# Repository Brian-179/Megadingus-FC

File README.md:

# Megadingus-FC
Megadingus flight controllers/altimeters

(OUTDATED) FC1.5: Mostly tested, i2C bus is having an error, SPI untested and UART/USB works fine.

FC2.1: Fully ground tested but not flight proven under TVC. TVC flight imminent.

3 pyro channels

WiFi (ESP8266)

Main MCU is an RP2040

Main power connector is an XT30 (2-5S, 6S if you're willing to take the risk)

USB Mini B port

BMI088 IMU, BME280 Barometer

3 servo outputs

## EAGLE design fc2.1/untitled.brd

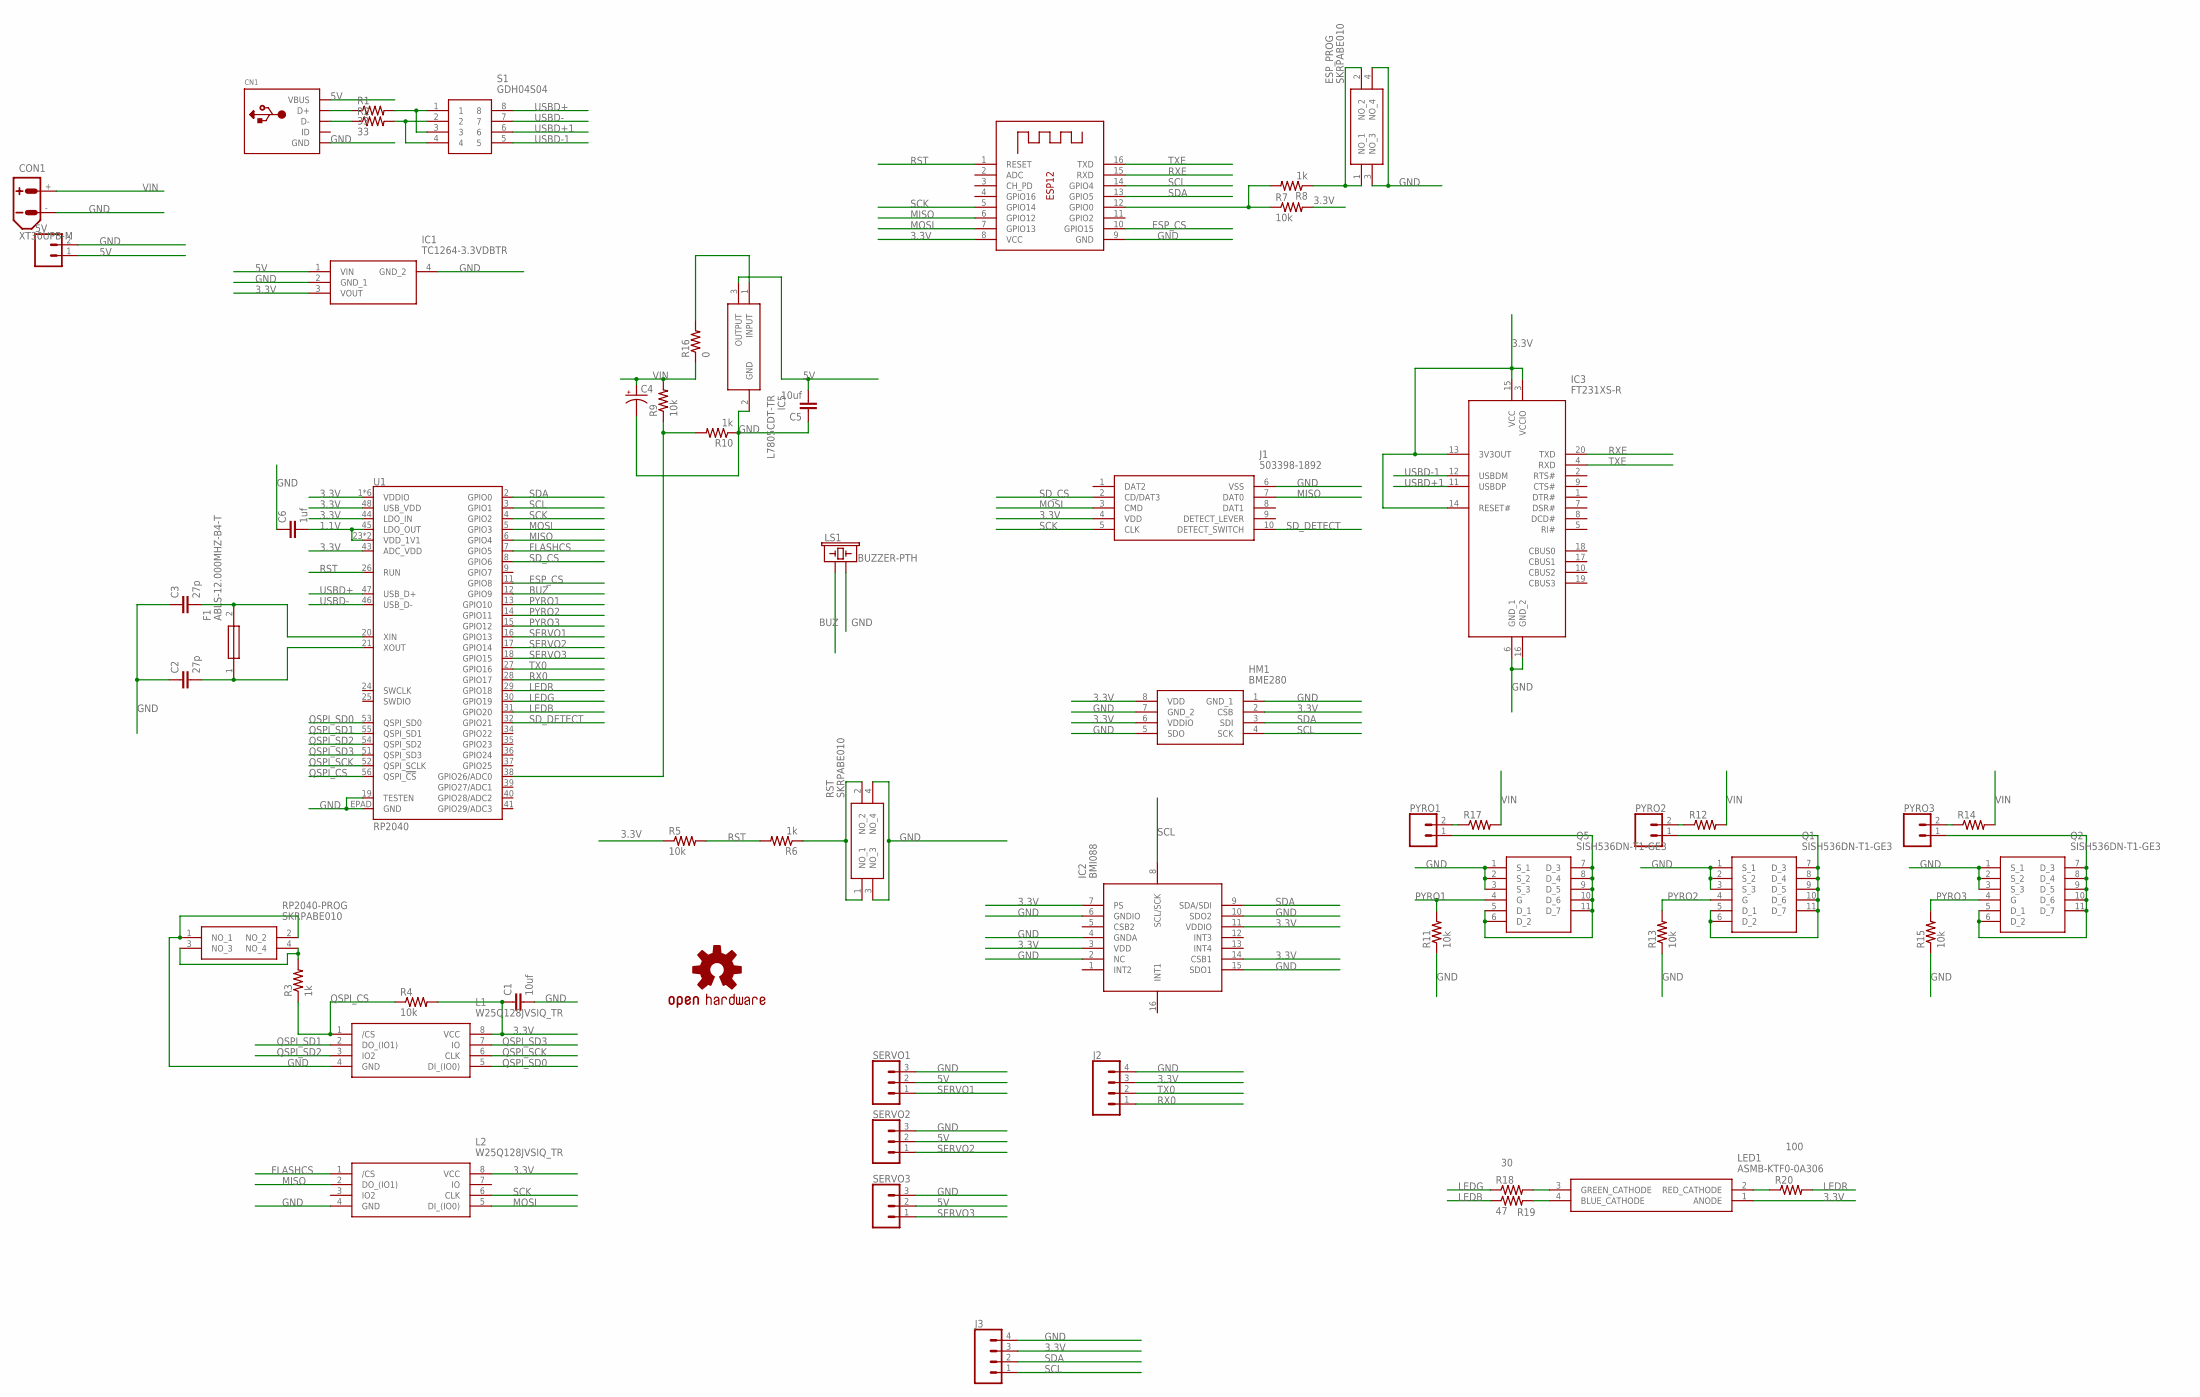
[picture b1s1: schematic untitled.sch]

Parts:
5V: CONN_02; 1X02
C1, C5: 10uf; C0805
C2, C3: 27p; C0805
C4: CPOL-USE3.5-8; E3,5-8
C6: 1uf; C0805
CN1: USBMINIB; USB-MINIB
CON1: XT30UPB-M
ESP_PROG: SKRPABE010
F1: ABLS-12.000MHZ-B4-T; HC/49US-(AT49)_1
HM1: BME280
IC1: TC1264-3.3VDBTR; SOT230P700X180-4N
IC2: BMI088
IC3: FT231XS-R; SOP64P599X175-20N
IC5: L7805CDT-TR; L7805CDTTR
J1: 503398-1892
J2, J3: CONN_04; 1X04
L1, L2: W25Q128JVSIQ_TR; SOIC127P780X195-8N
LED1: ASMB-KTF0-0A306; ASMBKTF00A306
LOGO1: OSHW-LOGOS; OSHW-LOGO-S
LS1: BUZZER-PTH; BUZZER-12MM
PYRO1, PYRO2, PYRO3: CONN_025MM; SCREWTERMINAL-5MM-2
Q1, Q2, Q5: SISH536DN-T1-GE3; SQSA80ENWT1_GE3
R1, R2: 33; M0805
R3, R6, R8, R10: 1k; M0805
R4, R5, R7, R9, R11, R13, R15: 10k; M0805
R12, R14, R16, R17: 0; R2512
R18: 30; M0805
R19: 47; M0805
R20: 100; M0805
RP2040-PROG: SKRPABE010
RST: SKRPABE010
S1: GDH04S04; SOIC127P813X256-8N
SERVO1, SERVO2, SERVO3: CONN_03; 1X03
U1: RP2040; QFN-56
X1: ESP-12

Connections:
1.1V: C6.2, U1.23 (VDD_1V1), U1.45 (LDO_OUT), U1.50 (VDD_1V1)
3.3V: C1.1, HM1.2 (CSB), HM1.6 (VDDIO), HM1.8 (VDD), IC1.3 (VOUT), IC2.3 (VDD), IC2.7 (PS), IC2.11 (VDDIO), IC2.14 (CSB1), IC3.3 (VCCIO), IC3.13 (3V3OUT), IC3.14 (RESET#), IC3.15 (VCC), J1.4 (VDD), J2.3, J3.3, L1.8 (VCC), L2.8 (VCC), LED1.1 (ANODE), R4.2, R5.1, R7.2, U1.1 (VDDIO), U1.10 (VDDIO), U1.22 (VDDIO), U1.33 (VDDIO), U1.42 (VDDIO), U1.43 (ADC_VDD), U1.44 (LDO_IN), U1.48 (USB_VDD), U1.49 (VDDIO), X1.8 (VCC)
5V: 5V.1, C5.2, CN1.VBUS, IC1.1 (VIN), IC5.3 (OUTPUT), SERVO1.2, SERVO2.2, SERVO3.2
BUZ: LS1.+ (1), U1.12 (GPIO9)
ESP_CS: U1.11 (GPIO8), X1.10 (GPIO15)
FLASHCS: L2.1 (/CS), U1.7 (GPIO5)
GND: 5V.2, C1.2, C2.1, C3.1, C4.-, C5.1, C6.1, CN1.GND, CON1.-, ESP_PROG.3 (NO_3), ESP_PROG.4 (NO_4), HM1.1 (GND_1), HM1.5 (SDO), HM1.7 (GND_2), IC1.2 (GND_1), IC1.4 (GND_2), IC2.2 (NC), IC2.4 (GNDA), IC2.6 (GNDIO), IC2.10 (SDO2), IC2.15 (SDO1), IC3.6 (GND_1), IC3.16 (GND_2), IC5.2 (GND), J1.6 (VSS), J2.4, J3.4, L1.4 (GND), L2.4 (GND), LS1.- (2), Q1.1 (S_1), Q1.2 (S_2), Q1.3 (S_3), Q2.1 (S_1), Q2.2 (S_2), Q2.3 (S_3), Q5.1 (S_1), Q5.2 (S_2), Q5.3 (S_3), R10.1, R11.1, R13.1, R15.1, RP2040-PROG.1 (NO_1), RP2040-PROG.2 (NO_2), RST.3 (NO_3), RST.4 (NO_4), SERVO1.3, SERVO2.3, SERVO3.3, U1.19 (TESTEN), U1.EPAD (GND), X1.9 (GND)
LEDB: R19.1, U1.31 (GPIO20)
LEDG: R18.1, U1.30 (GPIO19)
LEDR: R20.2, U1.29 (GPIO18)
MISO: J1.7 (DAT0), L2.2 (DO_(IO1)), U1.6 (GPIO4), X1.6 (GPIO12)
MOSI: J1.3 (CMD), L2.5 (DI_(IO0)), U1.5 (GPIO3), X1.7 (GPIO13)
unnamed: PYRO2.2, R12.1
unnamed: R3.2, RP2040-PROG.3 (NO_3), RP2040-PROG.4 (NO_4)
unnamed: ESP_PROG.1 (NO_1), ESP_PROG.2 (NO_2), R8.1
unnamed: R6.1, RST.1 (NO_1), RST.2 (NO_2)
unnamed: CN1.D+, R1.1
unnamed: CN1.D-, R2.1
unnamed: PYRO2.1, Q1.5 (D_1), Q1.6 (D_2), Q1.7 (D_3), Q1.8 (D_4), Q1.9 (D_5), Q1.10 (D_6), Q1.11 (D_7)
unnamed: PYRO3.2, R14.1
unnamed: PYRO1.1, Q5.5 (D_1), Q5.6 (D_2), Q5.7 (D_3), Q5.8 (D_4), Q5.9 (D_5), Q5.10 (D_6), Q5.11 (D_7)
unnamed: R7.1, R8.2, X1.12 (GPIO0)
unnamed: PYRO3.1, Q2.5 (D_1), Q2.6 (D_2), Q2.7 (D_3), Q2.8 (D_4), Q2.9 (D_5), Q2.10 (D_6), Q2.11 (D_7)
unnamed: R1.2, S1.1, S1.3
unnamed: IC5.1 (INPUT), R16.2
unnamed: PYRO1.2, R17.1
unnamed: R2.2, S1.2, S1.4
unnamed: C3.2, F1.2, U1.20 (XIN)
unnamed: C2.2, F1.1, U1.21 (XOUT)
unnamed: LED1.3 (GREEN_CATHODE), R18.2
unnamed: R9.1, R10.2, U1.38 (GPIO26/ADC0)
unnamed: LED1.4 (BLUE_CATHODE), R19.2
unnamed: LED1.2 (RED_CATHODE), R20.1
PYRO1: Q5.4 (G), R11.2, U1.13 (GPIO10)
PYRO2: Q1.4 (G), R13.2, U1.14 (GPIO11)
PYRO3: Q2.4 (G), R15.2, U1.15 (GPIO12)
QSPI_CS: L1.1 (/CS), R3.1, R4.1, U1.56 (QSPI_!CS!)
QSPI_SCK: L1.6 (CLK), U1.52 (QSPI_SCLK)
QSPI_SD0: L1.5 (DI_(IO0)), U1.53 (QSPI_SD0)
QSPI_SD1: L1.2 (DO_(IO1)), U1.55 (QSPI_SD1)
QSPI_SD2: L1.3 (IO2), U1.54 (QSPI_SD2)
QSPI_SD3: L1.7 (IO), U1.51 (QSPI_SD3)
RST: R5.2, R6.2, U1.26 (RUN), X1.1 (RESET)
RX0: J2.1, U1.28 (GPIO17)
RXE: IC3.20 (TXD), X1.15 (RXD)
SCK: J1.5 (CLK), L2.6 (CLK), U1.4 (GPIO2), X1.5 (GPIO14)
SCL: HM1.4 (SCK), IC2.8 (SCL/SCK), J3.1, U1.3 (GPIO1), X1.14 (GPIO4)
SDA: HM1.3 (SDI), IC2.9 (SDA/SDI), J3.2, U1.2 (GPIO0), X1.13 (GPIO5)
SD_CS: J1.2 (CD/DAT3), U1.8 (GPIO6)
SD_DETECT: J1.10 (DETECT_SWITCH), U1.32 (GPIO21)
SERVO1: SERVO1.1, U1.16 (GPIO13)
SERVO2: SERVO2.1, U1.17 (GPIO14)
SERVO3: SERVO3.1, U1.18 (GPIO15)
TX0: J2.2, U1.27 (GPIO16)
TXE: IC3.4 (RXD), X1.16 (TXD)
USBD+: S1.8, U1.47 (USB_D+)
USBD+1: IC3.11 (USBDP), S1.6
USBD-: S1.7, U1.46 (USB_D-)
USBD-1: IC3.12 (USBDM), S1.5
VIN: C4.+, CON1.+, R9.2, R12.2, R14.2, R16.1, R17.2

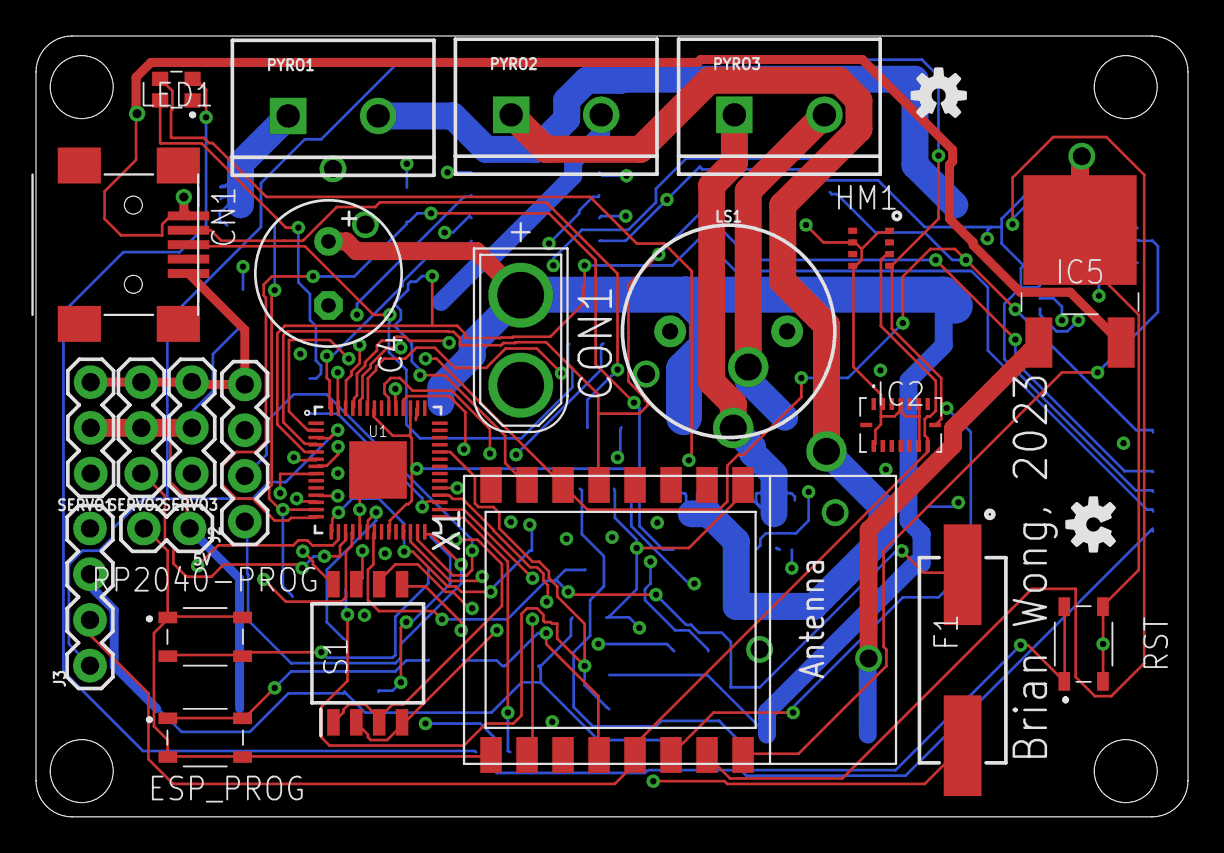
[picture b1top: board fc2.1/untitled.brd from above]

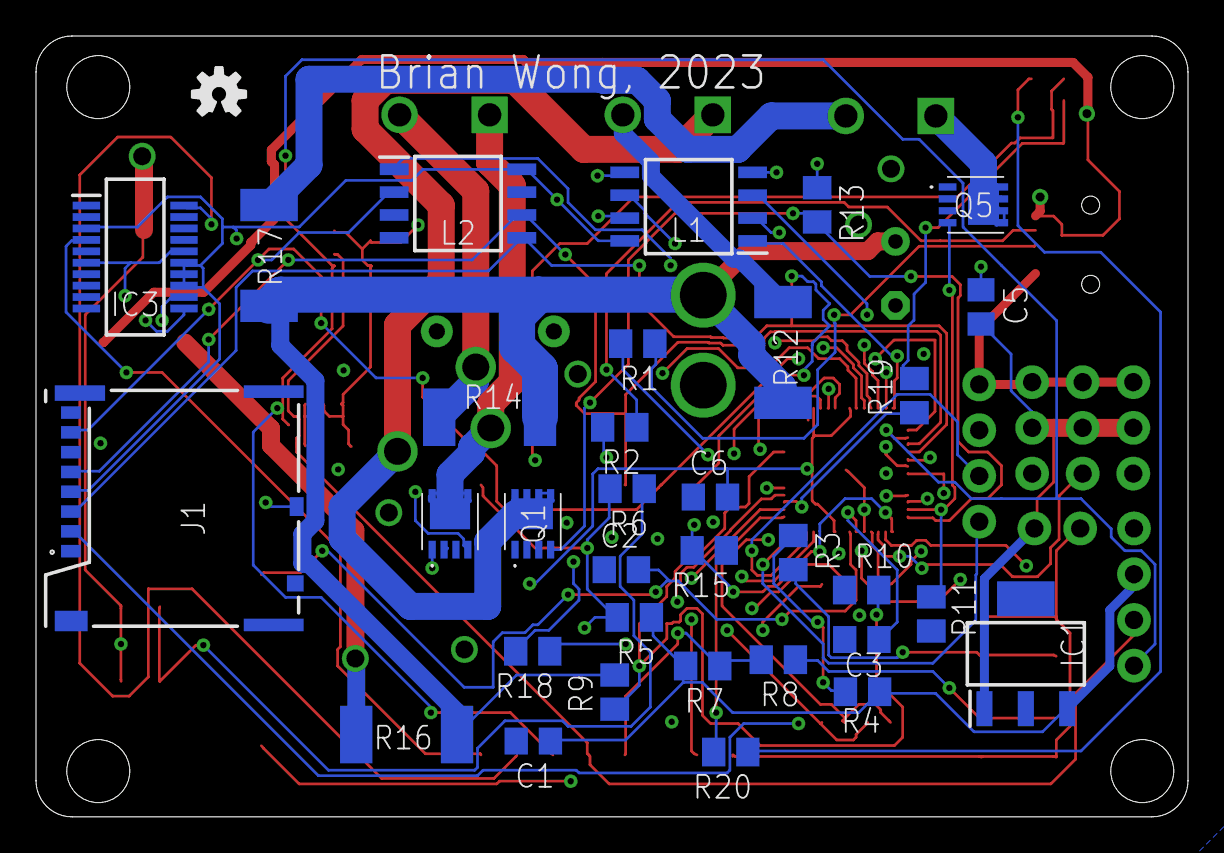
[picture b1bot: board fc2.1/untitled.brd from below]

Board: 4 copper layers, 64.0 x 43.4 mm, 60 parts (34 on the bottom side), 60 nets.

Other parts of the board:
LOGO2, LOGO3: OSHW-LOGOS; OSHW-LOGO-S

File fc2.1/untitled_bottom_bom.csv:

Comment,Designator,Footprint,LCSC Part #
0,R12 R14 R16 R17,R2512,
1k,R3 R6 R8 R10,M0805,
1uf,C6,C0805,
10k,R4 R5 R7 R9 R11 R13 R15,M0805,
10uf,C1 C5,C0805,
27p,C2 C3,C0805,
30,R18,M0805,
33,R1 R2,M0805,
47,R19,M0805,
100,R20,M0805,
503398-1892,J1,503398-1892,
FT231XS-R,IC3,SOP64P599X175-20N,
SISH536DN-T1-GE3,Q1 Q2 Q5,SQSA80ENWT1_GE3,
TC1264-3.3VDBTR,IC1,SOT230P700X180-4N,
W25Q128JVSIQ_TR,L1 L2,SOIC127P780X195-8N,

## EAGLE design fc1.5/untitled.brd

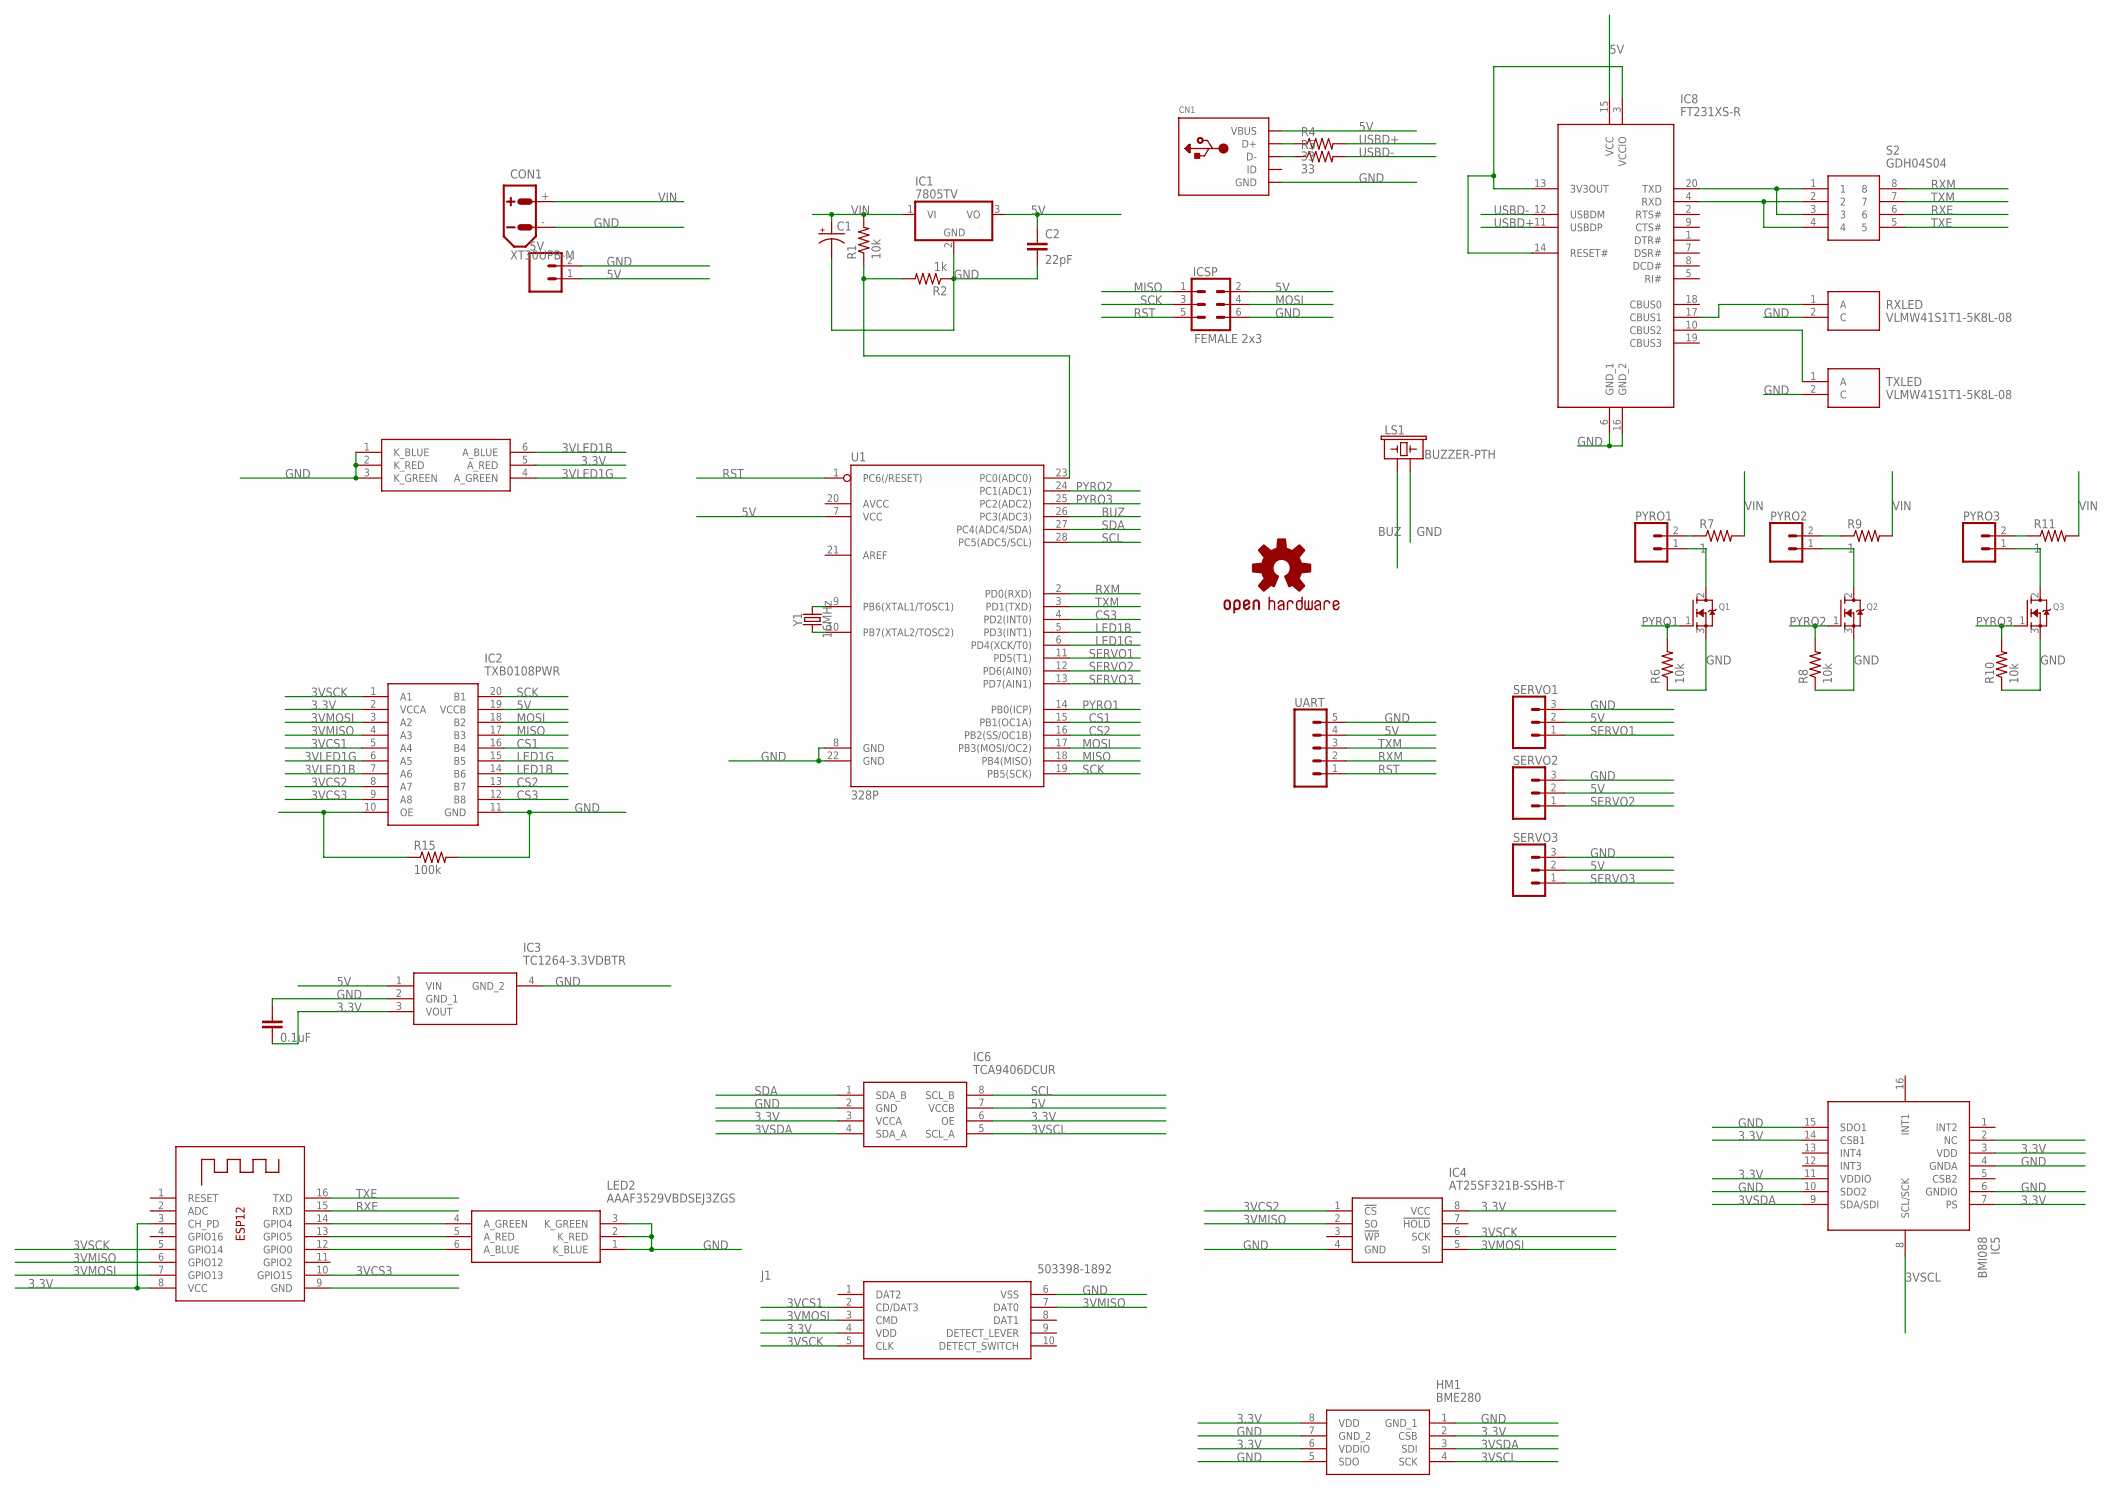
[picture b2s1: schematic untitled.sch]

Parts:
5V: CONN_02; 1X02
C1: CPOL-USE3.5-8; E3,5-8
C2: 22pF; CAP-PTH-2.54
C4: 0.1uF; CAP-PTH-SMALL-KIT
CN1: USBMINIB; USB-MINIB
CON1: XT30UPB-M
HM1: BME280
IC1: 7805TV; TO220V
IC2: TXB0108PWR; SOP65P640X120-20N
IC3: TC1264-3.3VDBTR; SOT230P700X180-4N
IC4: AT25SF321B-SSHB-T; SOIC127P600X175-8N
IC5: BMI088
IC6: TCA9406DCUR; SOP50P310X90-8N
IC8: FT231XS-R; SOP64P599X175-20N
ICSP: FEMALE 2x3; 2X3
J1: 503398-1892
LED1, LED2: AAAF3529VBDSEJ3ZGS
LOGO1: OSHW-LOGOL; OSHW-LOGO-L
LS1: BUZZER-PTH; BUZZER-12MM
PYRO1, PYRO2, PYRO3: CONN_025MM; SCREWTERMINAL-5MM-2
Q1, Q2, Q3: MOSFET-NGDS_TO220V; TO220V
R1, R6, R8, R10: 10k; 0805-THM
R2: 1k; 0805-THM
R4, R5: 33; 0805-THM
R7, R9, R11: 1; 0805-THM
R15: 100k; 0805-THM
RXLED: VLMW41S1T1-5K8L-08; LEDM3528X185N
S2: GDH04S04; SOIC127P813X256-8N
SERVO1, SERVO2, SERVO3: CONN_03; 1X03
TXLED: VLMW41S1T1-5K8L-08; LEDM3528X185N
U1: 328P; DIP28
UART: CONN_05; 1X05
X1: ESP-12
Y1: 16MHz; HC49US

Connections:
3.3V: C4.2, HM1.2 (CSB), HM1.6 (VDDIO), HM1.8 (VDD), IC2.2 (VCCA), IC3.3 (VOUT), IC4.8 (VCC), IC5.3 (VDD), IC5.7 (PS), IC5.11 (VDDIO), IC5.14 (CSB1), IC6.3 (VCCA), IC6.6 (OE), J1.4 (VDD), LED1.5 (A_RED), X1.3 (CH_PD), X1.8 (VCC)
3VCS1: IC2.5 (A4), J1.2 (CD/DAT3)
3VCS2: IC2.8 (A7), IC4.1 (!CS)
3VCS3: IC2.9 (A8), X1.10 (GPIO15)
3VLED1B: IC2.7 (A6), LED1.6 (A_BLUE)
3VLED1G: IC2.6 (A5), LED1.4 (A_GREEN)
3VMISO: IC2.4 (A3), IC4.2 (SO), J1.7 (DAT0), X1.6 (GPIO12)
3VMOSI: IC2.3 (A2), IC4.5 (SI), J1.3 (CMD), X1.7 (GPIO13)
3VSCK: IC2.1 (A1), IC4.6 (SCK), J1.5 (CLK), X1.5 (GPIO14)
3VSCL: HM1.4 (SCK), IC5.8 (SCL/SCK), IC6.5 (SCL_A)
3VSDA: HM1.3 (SDI), IC5.9 (SDA/SDI), IC6.4 (SDA_A)
5V: 5V.1, C2.1, CN1.VBUS, IC1.3 (VO), IC2.19 (VCCB), IC3.1 (VIN), IC6.7 (VCCB), IC8.15 (VCC), ICSP.2, SERVO1.2, SERVO2.2, SERVO3.2, U1.7 (VCC), UART.4
BUZ: LS1.+ (1), U1.26 (PC3(ADC3))
CS1: IC2.16 (B4), U1.15 (PB1(OC1A))
CS2: IC2.13 (B7), U1.16 (PB2(SS/OC1B))
CS3: IC2.12 (B8), U1.4 (PD2(INT0))
GND: 5V.2, C1.-, C2.2, C4.1, CN1.GND, CON1.-, HM1.1 (GND_1), HM1.5 (SDO), HM1.7 (GND_2), IC1.2 (GND), IC2.11 (GND), IC3.2 (GND_1), IC3.4 (GND_2), IC4.4 (GND), IC5.4 (GNDA), IC5.6 (GNDIO), IC5.10 (SDO2), IC5.15 (SDO1), IC6.2 (GND), IC8.6 (GND_1), IC8.16 (GND_2), ICSP.6, J1.6 (VSS), LED1.1 (K_BLUE), LED1.2 (K_RED), LED1.3 (K_GREEN), LED2.1 (K_BLUE), LED2.2 (K_RED), LED2.3 (K_GREEN), LS1.- (2), Q1.3 (S), Q2.3 (S), Q3.3 (S), R2.1, R6.1, R8.1, R10.1, R15.2, RXLED.2 (C), SERVO1.3, SERVO2.3, SERVO3.3, TXLED.2 (C), U1.8 (GND), U1.22 (GND), UART.5, X1.9 (GND)
LED1B: IC2.14 (B6), U1.5 (PD3(INT1))
LED1G: IC2.15 (B5), U1.6 (PD4(XCK/T0))
MISO: IC2.17 (B3), ICSP.1, U1.18 (PB4(MISO))
MOSI: IC2.18 (B2), ICSP.4, U1.17 (PB3(MOSI/OC2))
unnamed: U1.9 (PB6(XTAL1/TOSC1)), Y1.2
unnamed: U1.10 (PB7(XTAL2/TOSC2)), Y1.1
unnamed: R1.1, R2.2, U1.23 (PC0(ADC0))
unnamed: CN1.D+, R4.1
unnamed: IC8.17 (CBUS1), RXLED.1 (A)
unnamed: IC8.20 (TXD), S2.1, S2.3
unnamed: IC8.4 (RXD), S2.2, S2.4
unnamed: IC8.3 (VCCIO), IC8.13 (3V3OUT), IC8.14 (RESET#)
unnamed: CN1.D-, R5.1
unnamed: IC8.10 (CBUS2), TXLED.1 (A)
unnamed: LED2.4 (A_GREEN), X1.14 (GPIO4)
unnamed: LED2.5 (A_RED), X1.13 (GPIO5)
unnamed: IC2.10 (OE), R15.1
unnamed: PYRO1.1, Q1.2 (D)
unnamed: PYRO1.2, R7.1
unnamed: PYRO2.1, Q2.2 (D)
unnamed: PYRO2.2, R9.1
unnamed: PYRO3.1, Q3.2 (D)
unnamed: PYRO3.2, R11.1
unnamed: LED2.6 (A_BLUE), X1.12 (GPIO0)
PYRO1: Q1.1 (G), R6.2, U1.14 (PB0(ICP))
PYRO2: Q2.1 (G), R8.2, U1.24 (PC1(ADC1))
PYRO3: Q3.1 (G), R10.2, U1.25 (PC2(ADC2))
RST: ICSP.5, U1.1 (PC6(/RESET)), UART.1
RXE: S2.6, X1.15 (RXD)
RXM: S2.8, U1.2 (PD0(RXD)), UART.2
SCK: IC2.20 (B1), ICSP.3, U1.19 (PB5(SCK))
SCL: IC6.8 (SCL_B), U1.28 (PC5(ADC5/SCL))
SDA: IC6.1 (SDA_B), U1.27 (PC4(ADC4/SDA))
SERVO1: SERVO1.1, U1.11 (PD5(T1))
SERVO2: SERVO2.1, U1.12 (PD6(AIN0))
SERVO3: SERVO3.1, U1.13 (PD7(AIN1))
TXE: S2.5, X1.16 (TXD)
TXM: S2.7, U1.3 (PD1(TXD)), UART.3
USBD+: IC8.11 (USBDP), R4.2
USBD-: IC8.12 (USBDM), R5.2
VIN: C1.+, CON1.+, IC1.1 (VI), R1.2, R7.2, R9.2, R11.2

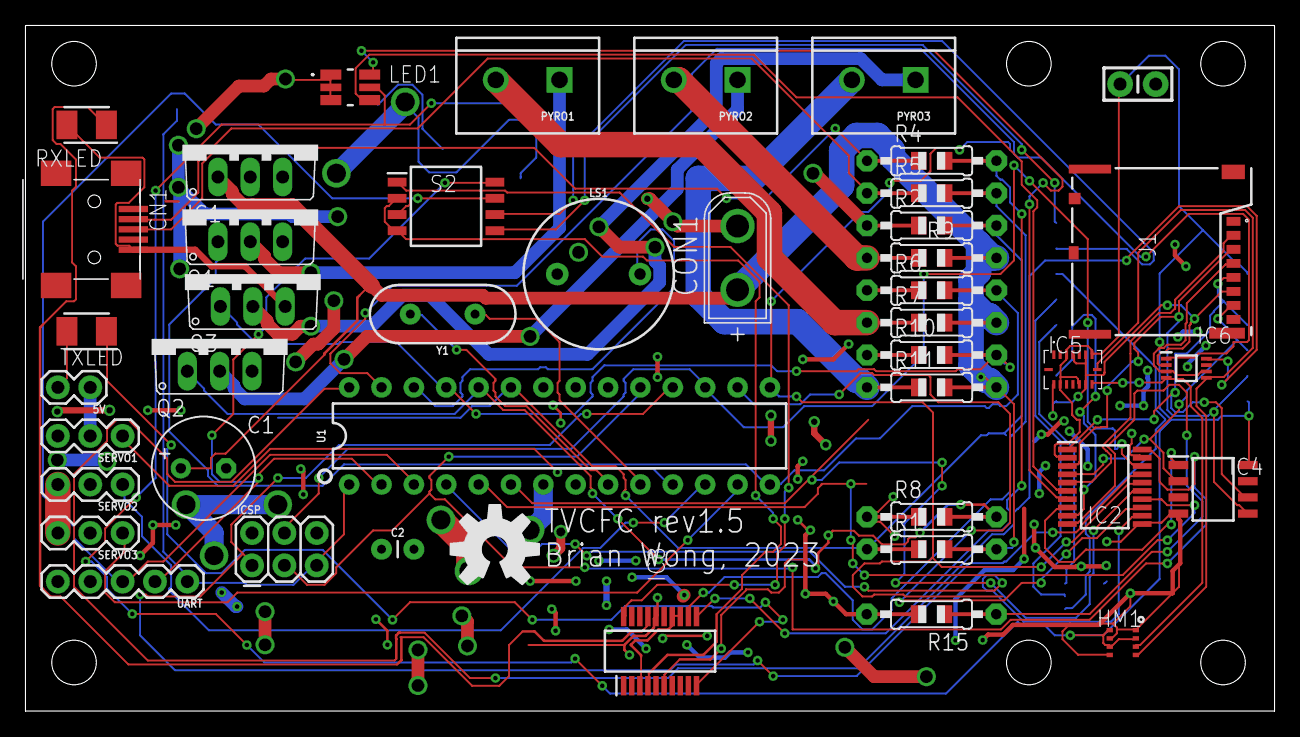
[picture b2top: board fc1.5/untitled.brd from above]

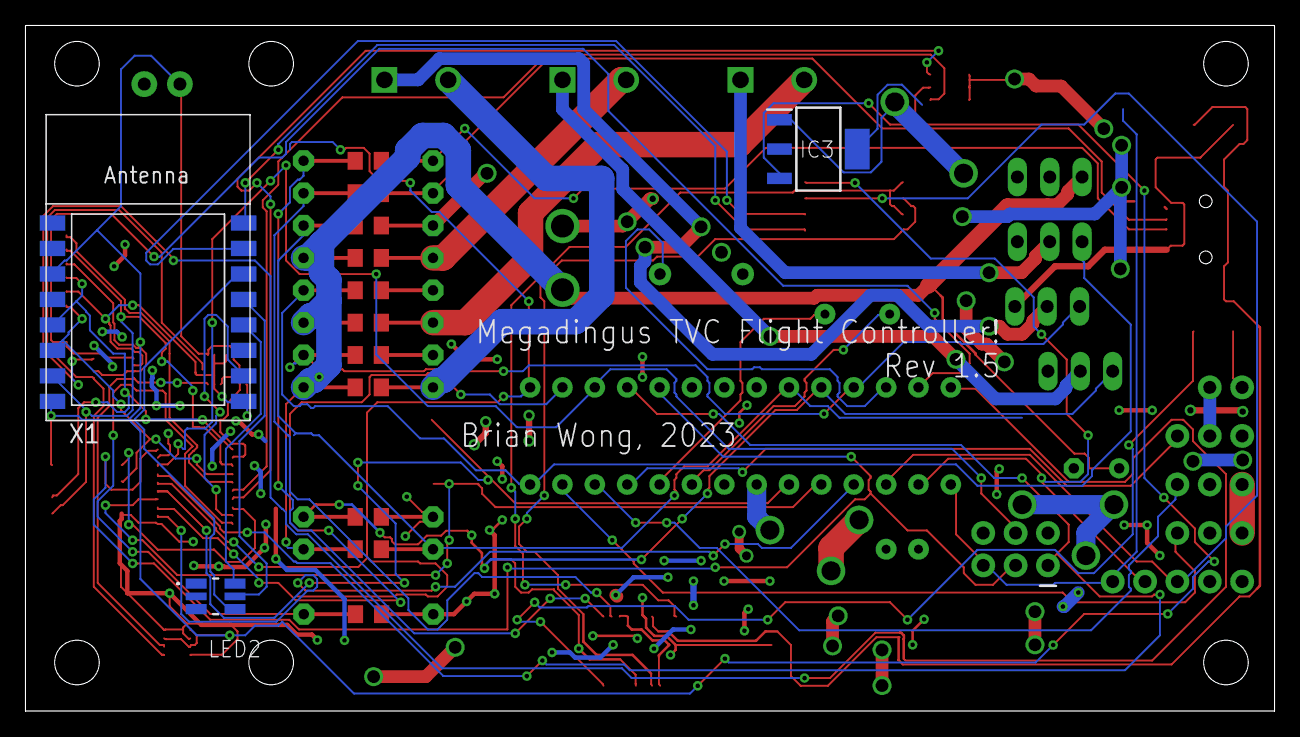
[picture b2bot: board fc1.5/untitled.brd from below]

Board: 2 copper layers, 98.0 x 53.8 mm, 47 parts (3 on the bottom side), 58 nets.

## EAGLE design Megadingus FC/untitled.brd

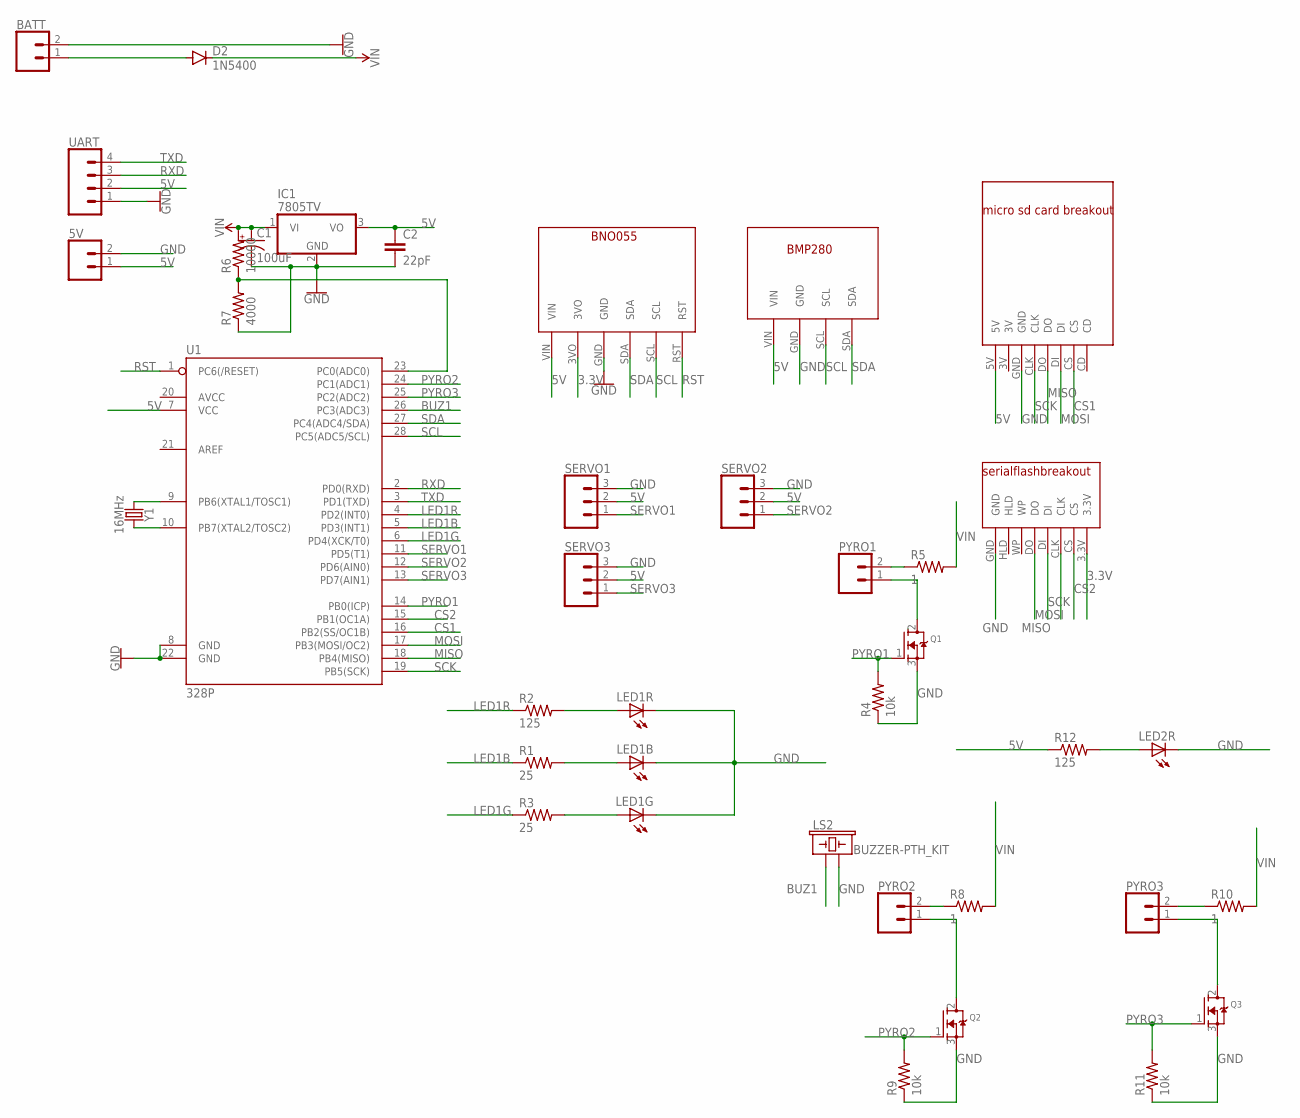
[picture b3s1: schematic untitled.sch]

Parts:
5V: CONN_02; 1X02
BATT: CONN_02; 1X02
C1: 100uF; CPOL-RADIAL-2.5MM-6.5MM
C2: 22pF; CAP-PTH-2.54
D2: 1N5400; DO201-15
IC1: 7805TV; TO220V
LED1B: LED1B; LED5MM
LED1G: LED1G; LED5MM
LED1R, LED2R: LED1R; LED5MM
LS2: BUZZER-PTH_KIT; BUZZER-12MM-KIT
PYRO1, PYRO2, PYRO3: CONN_02; 1X02
Q1, Q2, Q3: MOSFET-NGDS_TO220V; TO220V
R1, R3: 25; 0805-THM
R2, R12: 125; 0805-THM
R4, R9, R11: 10k; 0805-THM
R5, R8, R10: 1; 0805-THM
R6: 10000; 0805-THM
R7: 4000; 0805-THM
SERVO1, SERVO2, SERVO3: CONN_03; 1X03
U1: 328P; DIP28
U$1: BNO055
U$2: BMP280
U$3: ADAFRUITSDCARD
U$4: SPARKFUNFLASHBREAKOUT
UART: CONN_04PTH; 1X04
Y1: 16MHz; HC49US

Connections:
3.3V: U$1.3VO, U$4.3.3V
5V: 5V.1, C2.1, IC1.3 (VO), R12.1, SERVO1.2, SERVO2.2, SERVO3.2, U1.7 (VCC), U$1.VIN, U$2.VIN, U$3.5V, UART.2
BUZ1: LS2.+ (1), U1.26 (PC3(ADC3))
CS1: U1.16 (PB2(SS/OC1B)), U$3.CS
CS2: U1.15 (PB1(OC1A)), U$4.CS
GND: 5V.2, BATT.2, C1.2 (-), C2.2, IC1.2 (GND), LED1B.K (C), LED1G.K (C), LED1R.K (C), LED2R.K (C), LS2.- (2), Q1.3 (S), Q2.3 (S), Q3.3 (S), R4.1, R7.1, R9.1, R11.1, SERVO1.3, SERVO2.3, SERVO3.3, U1.8 (GND), U1.22 (GND), U$1.GND, U$2.GND, U$3.GND, U$4.GND, UART.1
LED1B: R1.1, U1.5 (PD3(INT1))
LED1G: R3.1, U1.6 (PD4(XCK/T0))
LED1R: R2.1, U1.4 (PD2(INT0))
MISO: U1.18 (PB4(MISO)), U$3.DO, U$4.DO
MOSI: U1.17 (PB3(MOSI/OC2)), U$3.DI, U$4.DI
unnamed: PYRO1.1, Q1.2 (D)
unnamed: LED1R.A, R2.2
unnamed: LED1B.A, R1.2
unnamed: LED1G.A, R3.2
unnamed: PYRO1.2, R5.1
unnamed: R6.1, R7.2, U1.23 (PC0(ADC0))
unnamed: U1.9 (PB6(XTAL1/TOSC1)), Y1.1
unnamed: U1.10 (PB7(XTAL2/TOSC2)), Y1.2
unnamed: BATT.1, D2.A
unnamed: PYRO2.2, R8.1
unnamed: PYRO3.2, R10.1
unnamed: PYRO2.1, Q2.2 (D)
unnamed: PYRO3.1, Q3.2 (D)
unnamed: LED2R.A, R12.2
PYRO1: Q1.1 (G), R4.2, U1.14 (PB0(ICP))
PYRO2: Q2.1 (G), R9.2, U1.24 (PC1(ADC1))
PYRO3: Q3.1 (G), R11.2, U1.25 (PC2(ADC2))
RST: U1.1 (PC6(/RESET)), U$1.RST
RXD: U1.2 (PD0(RXD)), UART.3
SCK: U1.19 (PB5(SCK)), U$3.CLK, U$4.CLK
SCL: U1.28 (PC5(ADC5/SCL)), U$1.SCL, U$2.SCL
SDA: U1.27 (PC4(ADC4/SDA)), U$1.SDA, U$2.SDA
SERVO1: SERVO1.1, U1.11 (PD5(T1))
SERVO2: SERVO2.1, U1.12 (PD6(AIN0))
SERVO3: SERVO3.1, U1.13 (PD7(AIN1))
TXD: U1.3 (PD1(TXD)), UART.4
VIN: C1.1 (+), D2.C, IC1.1 (VI), R5.2, R6.2, R8.2, R10.2

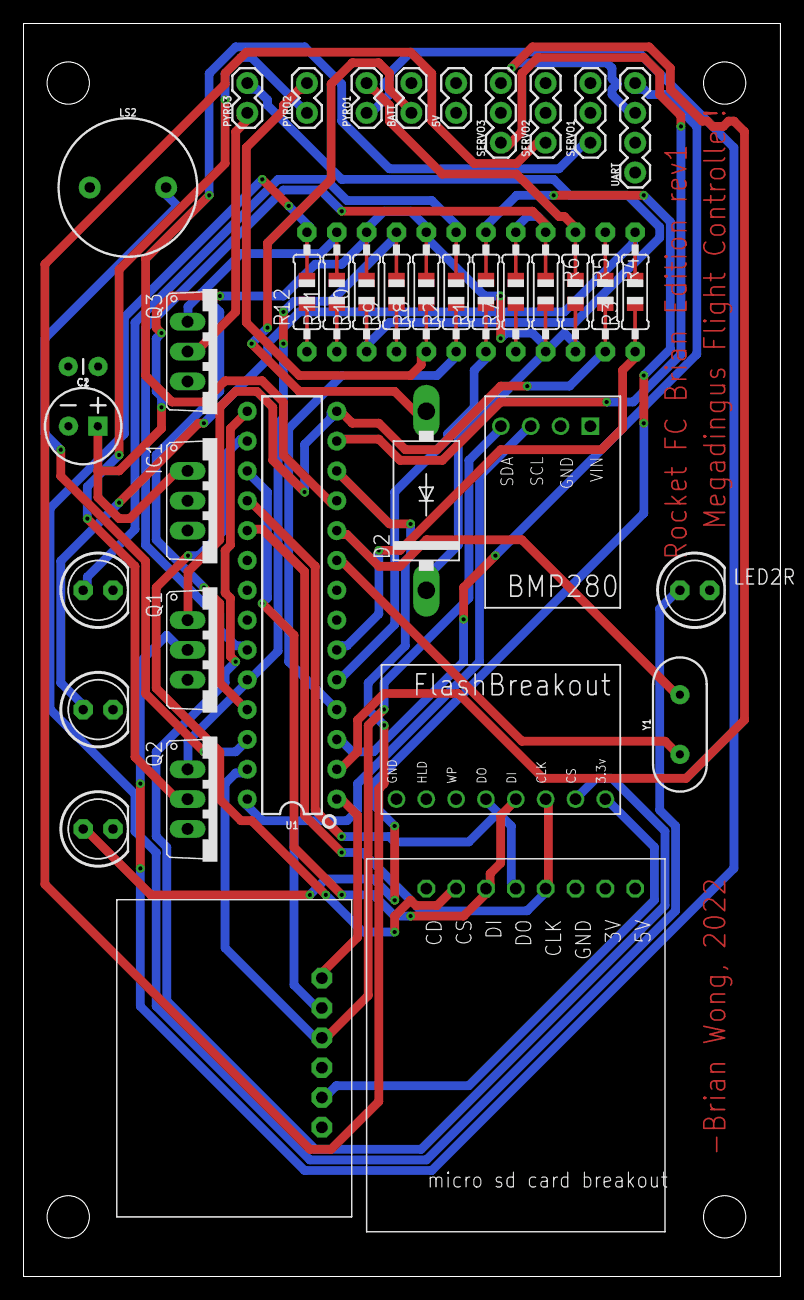
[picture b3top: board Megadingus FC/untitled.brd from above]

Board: 2 copper layers, 64.4 x 106.7 mm, 39 parts (0 on the bottom side), 38 nets.

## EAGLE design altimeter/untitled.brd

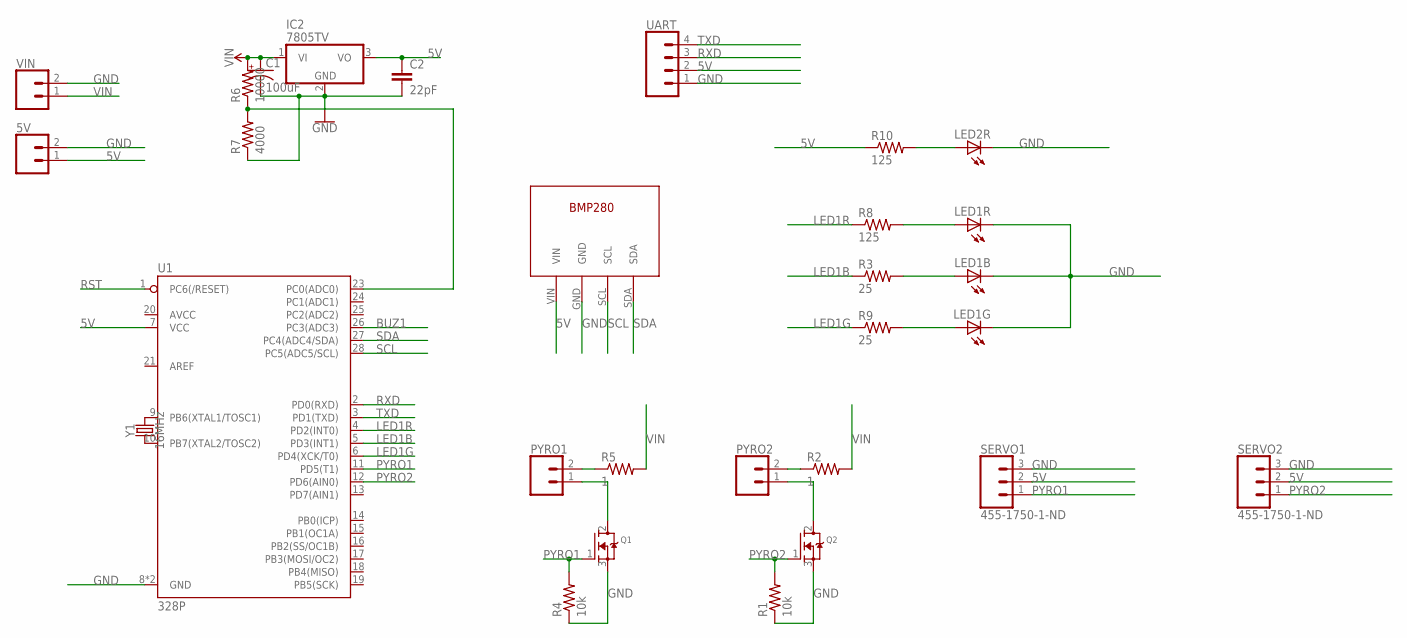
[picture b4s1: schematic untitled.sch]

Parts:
5V: CONN_02; 1X02
C1: 100uF; CPOL-RADIAL-2.5MM-6.5MM
C2: 22pF; CAP-PTH-2.54
IC2: 7805TV; TO220V
LED1B: LED1B; LED5MM
LED1G: LED1G; LED5MM
LED1R, LED2R: LED1R; LED5MM
PYRO1, PYRO2: CONN_02; 1X02
Q1, Q2: MOSFET-NGDS_TO220V; TO220V
R1, R4: 10k; 0805-THM
R2, R5: 1; 0805-THM
R3, R9: 25; 0805-THM
R6: 10000; 0805-THM
R7: 4000; 0805-THM
R8, R10: 125; 0805-THM
SERVO1, SERVO2: 455-1750-1-ND; 1X03
U1: 328P; DIP28
U$1: BMP280
UART: CONN_04PTH; 1X04
VIN: CONN_02; 1X02
Y1: 16MHz; HC49US

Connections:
5V: 5V.1, C2.1, IC2.3 (VO), R10.1, SERVO1.2, SERVO2.2, U1.7 (VCC), U$1.VIN, UART.2
BUZ1: U1.26 (PC3(ADC3))
GND: 5V.2, C1.2 (-), C2.2, IC2.2 (GND), LED1B.K (C), LED1G.K (C), LED1R.K (C), LED2R.K (C), Q1.3 (S), Q2.3 (S), R1.1, R4.1, R7.1, SERVO1.3, SERVO2.3, U1.8 (GND), U1.22 (GND), U$1.GND, UART.1, VIN.2
LED1B: R3.1, U1.5 (PD3(INT1))
LED1G: R9.1, U1.6 (PD4(XCK/T0))
LED1R: R8.1, U1.4 (PD2(INT0))
unnamed: PYRO1.1, Q1.2 (D)
unnamed: PYRO2.1, Q2.2 (D)
unnamed: U1.9 (PB6(XTAL1/TOSC1)), Y1.2
unnamed: U1.10 (PB7(XTAL2/TOSC2)), Y1.1
unnamed: PYRO1.2, R5.1
unnamed: R6.1, R7.2, U1.23 (PC0(ADC0))
unnamed: PYRO2.2, R2.1
unnamed: LED1R.A, R8.2
unnamed: LED1B.A, R3.2
unnamed: LED1G.A, R9.2
unnamed: LED2R.A, R10.2
PYRO1: Q1.1 (G), R4.2, SERVO1.1, U1.11 (PD5(T1))
PYRO2: Q2.1 (G), R1.2, SERVO2.1, U1.12 (PD6(AIN0))
RST: U1.1 (PC6(/RESET))
RXD: U1.2 (PD0(RXD)), UART.3
SCL: U1.28 (PC5(ADC5/SCL)), U$1.SCL
SDA: U1.27 (PC4(ADC4/SDA)), U$1.SDA
TXD: U1.3 (PD1(TXD)), UART.4
VIN: C1.1 (+), IC2.1 (VI), R2.2, R5.2, R6.2, VIN.1

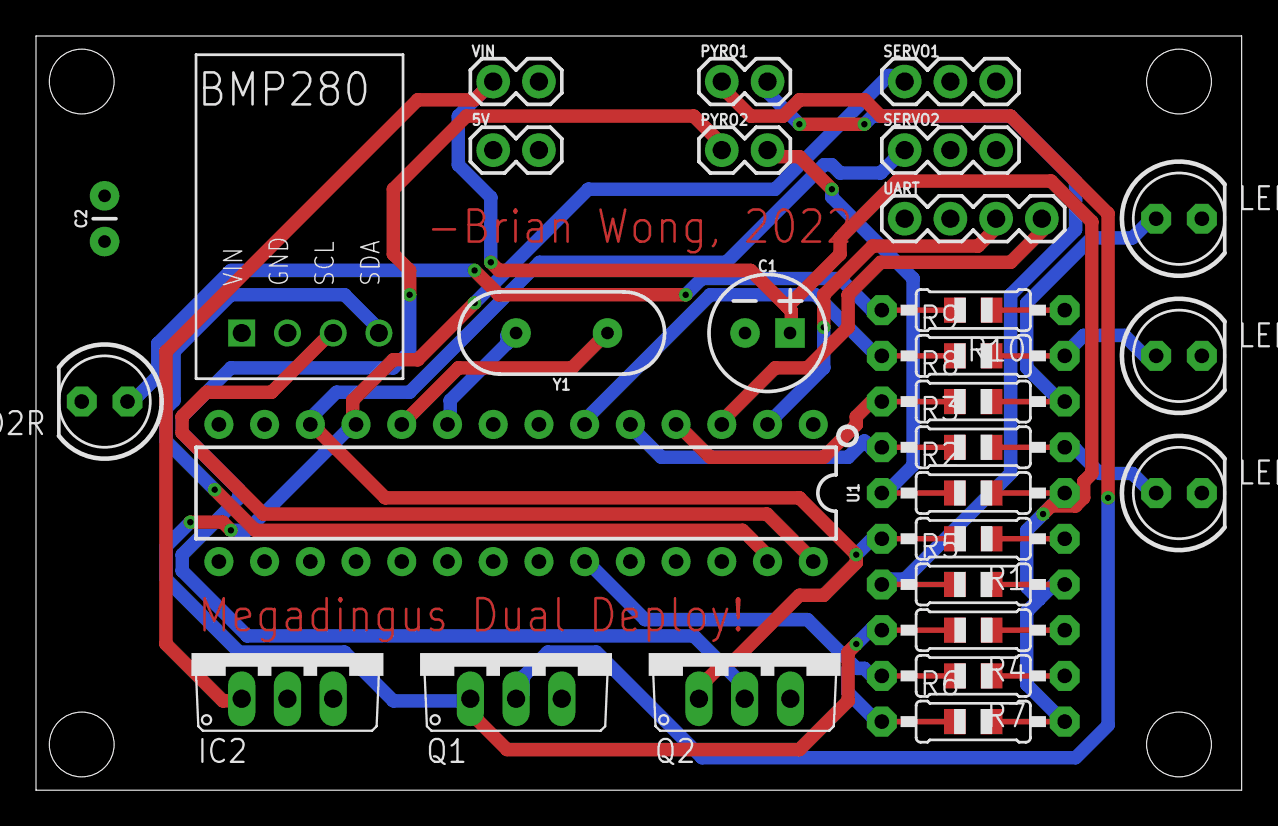
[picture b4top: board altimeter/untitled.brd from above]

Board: 2 copper layers, 67.0 x 41.9 mm, 29 parts (0 on the bottom side), 23 nets.

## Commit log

2023-04-05 Add files via upload
    Software is extremely experimental and untested. Responds on the ground fine but not flight tested yet.

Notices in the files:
parts and their libraries:
SparkFun-Connectors: Licensing: Creative Commons ShareAlike 4.0 International - https://creativecommons.org/licenses/by-sa/4.0
